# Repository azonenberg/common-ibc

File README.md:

# common-ibc

This is a 48-12V 72W non-isolated intermediate bus converter which I plan to use in all of my larger FPGA projects.

It uses a charge pump which has a fixed divide-by-4 output ratio rather than using a regulating buck topology. This
allows high efficiency but requires downstream loads to be able to tolerate a wider range of input voltages.

The architecture is scalable to 2 or 4 parallel converter modules, allowing 144W (12A) or 288W (24A) IBCs based on the
same chipset to be constructed in a straightforward manner based on a scaling of this design, however there are no
near-term plans to create such a converter since none of my near term project plans require that much power.

## Input

The input is +48VDC nominal on a 6-pin Molex Mini-Fit Jr connector, using a pinout compatible with the Mean Well
GST280A48-C6P power brick (and possibly others). The negative terminal of the input power connection is connected to
circuit ground.

The permissible operating range is 40 to 56VDC (corresponding to 10 to 14V output). An input protection circuit will
disable the converter if the input is out of this range.

The unregulated output voltage is 1/4 of the input, so if the load has tighter requirements for accuracy of the 12V
rail then this will further constrain the input supply voltage.

## Internal Construction

The converter is built around the Murata MYC0409-NA charge pump DC-DC module.

## Outputs

In addition to the high current 12V output (on an 8-pin Molex Mini-Fit Jr connector) the converter provides a 3.3V
standby rail (using the Cyntec MUN12AD03-SE regulating off of the 12V rail), capable of up to 3A, which is intended for
powering sleep/idle circuitry such as soft power on/off, rail sequencing, etc.

Both the primary 12V step-down converter and the 3.3V standby regulator are always enabled, however a load switch on
the main 12V output allows it to be disabled to completely power down the bulk of the downstream device, keeping only
the converter board and the 3V3_SB rail on the downstream device energized. The load switch has an integrated soft
start, preventing high current surges when charging bulk capacitance on the load.

## Monitoring

The onboard STM32L431 microcontroller monitors the PGOOD signals of internal regulators as well as the ALERT output
of the onboard AT30TS74 temperature sensor. It also continually uses an internal ADC to record the input and output
voltage, downstream load sense voltage, and input and output current. All of these sensor readings may be queried by
the load over the I2C management bus.

## Protection

The converter includes multiple levels of protection to minimize the risk of fire or equipment damage.

The most critical interlocks are implemented in hardware while additional protections with lower thresholds are
implemented in software on the management MCU.

If a software interlock triggers, the 12V output is disabled. The management MCU will automatically attempt to restart
the output (as long as the load is still requesting power) at periodic intervals once the fault condition is cleared.

The 3.3V standby output will remain active and the management MCU will remain operational while a software interlock is
tripped.

### Input overcurrent

The 48V input is fused at 2.5A using a socketed 5x20mm fast-blow fuse.

### Output overcurrent

The 12V primary output is fused at 10A using a soldered-down fast-blow fuse.

The 3.3V standby output is current limited (typical range 3.8 - 5.2A) by the DC-DC converter and does not have an
supplemental fuse.

If the 12V output current exceeds 6.5A, a software interlock is triggered. The output load switch also has a
short circuit protection feature, however the software interlock is intended to trip at a lower level.

### Regulator fault

If any of the internal regulators indicates a problem (PGOOD low) a software interlock is triggered.

### Over-temperature

If the AT30TS74 indicates an out-of-bounds temperature (ALERT low) a software interlock is triggered.

The MCU does not configure the AT30TS74; on power up the default over-temperature limit (80C) is active. This sensor is
located on the same I2C management bus as the MCU and may be reconfigured or queried by the load as required; the
IBC will activate the interlock if the programmed temperature range is exceeded.

### Input under / over voltage

The input is monitored by a TPS16630 protection controller, which also provides soft-start for the input bulk
capacitance. If the input voltage drops below 40V or rises above 56V (corresponding to 10-14V output) the system will
shut down completely (input power cut off upstream of the charge pump, disabling the microcontroller, 3.3V standby
rail, and all internal circuitry past the protection controller).

The input has a Schottky diode to ground in reverse polarity. If the input goes significantly negative (reverse
polarity connection) the diode will conduct and blow the input fuse, hopefully protecting the load and possibly even
the power supply from damage.

As an additional protection against catastrophic overvoltage at the input, a zener clamp will trip at approximately
58V, blowing the input fuse.

### Output under / over voltage

Since the output voltage is normally a fixed 4:1 scaling of the input, output voltage drifting beyond this range is
likely indicative of a failure of the charge pump module.

* If the 12V rail voltage drops below 10V, a software interlock is triggered.
* If the 12V rail voltage rises above 14V, a software interlock is triggered.
* If the 12V rail voltage rises above 17V a zener clamp on the output will begin to conduct, blowing the output fuse.

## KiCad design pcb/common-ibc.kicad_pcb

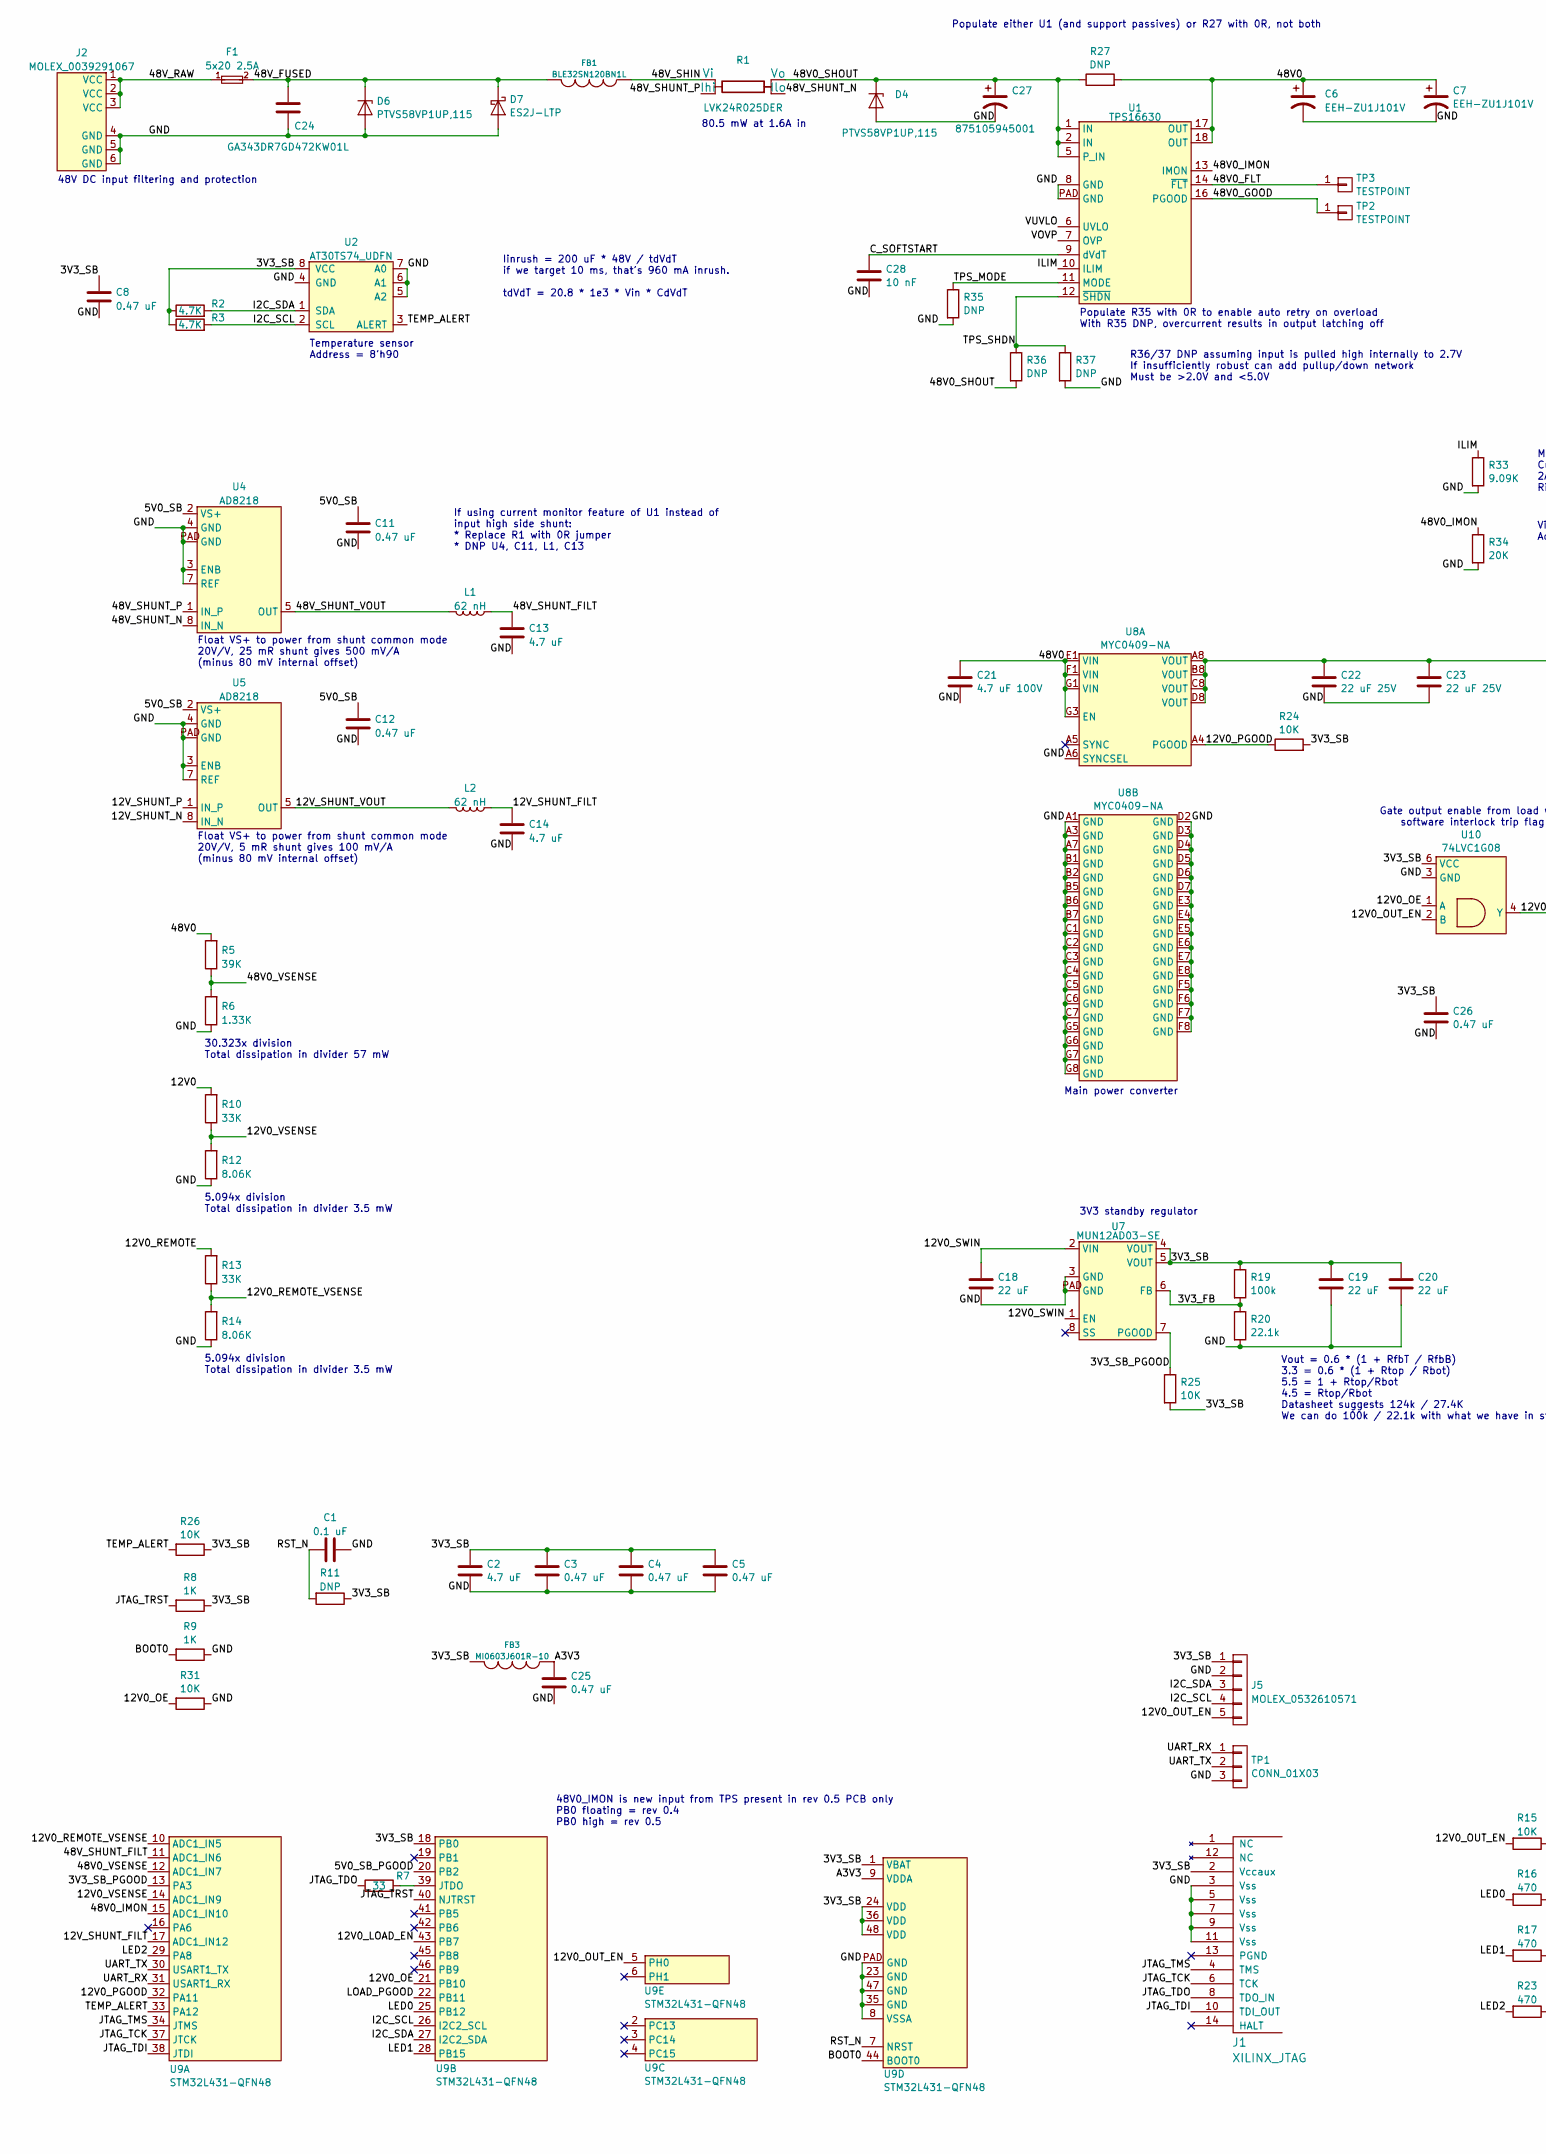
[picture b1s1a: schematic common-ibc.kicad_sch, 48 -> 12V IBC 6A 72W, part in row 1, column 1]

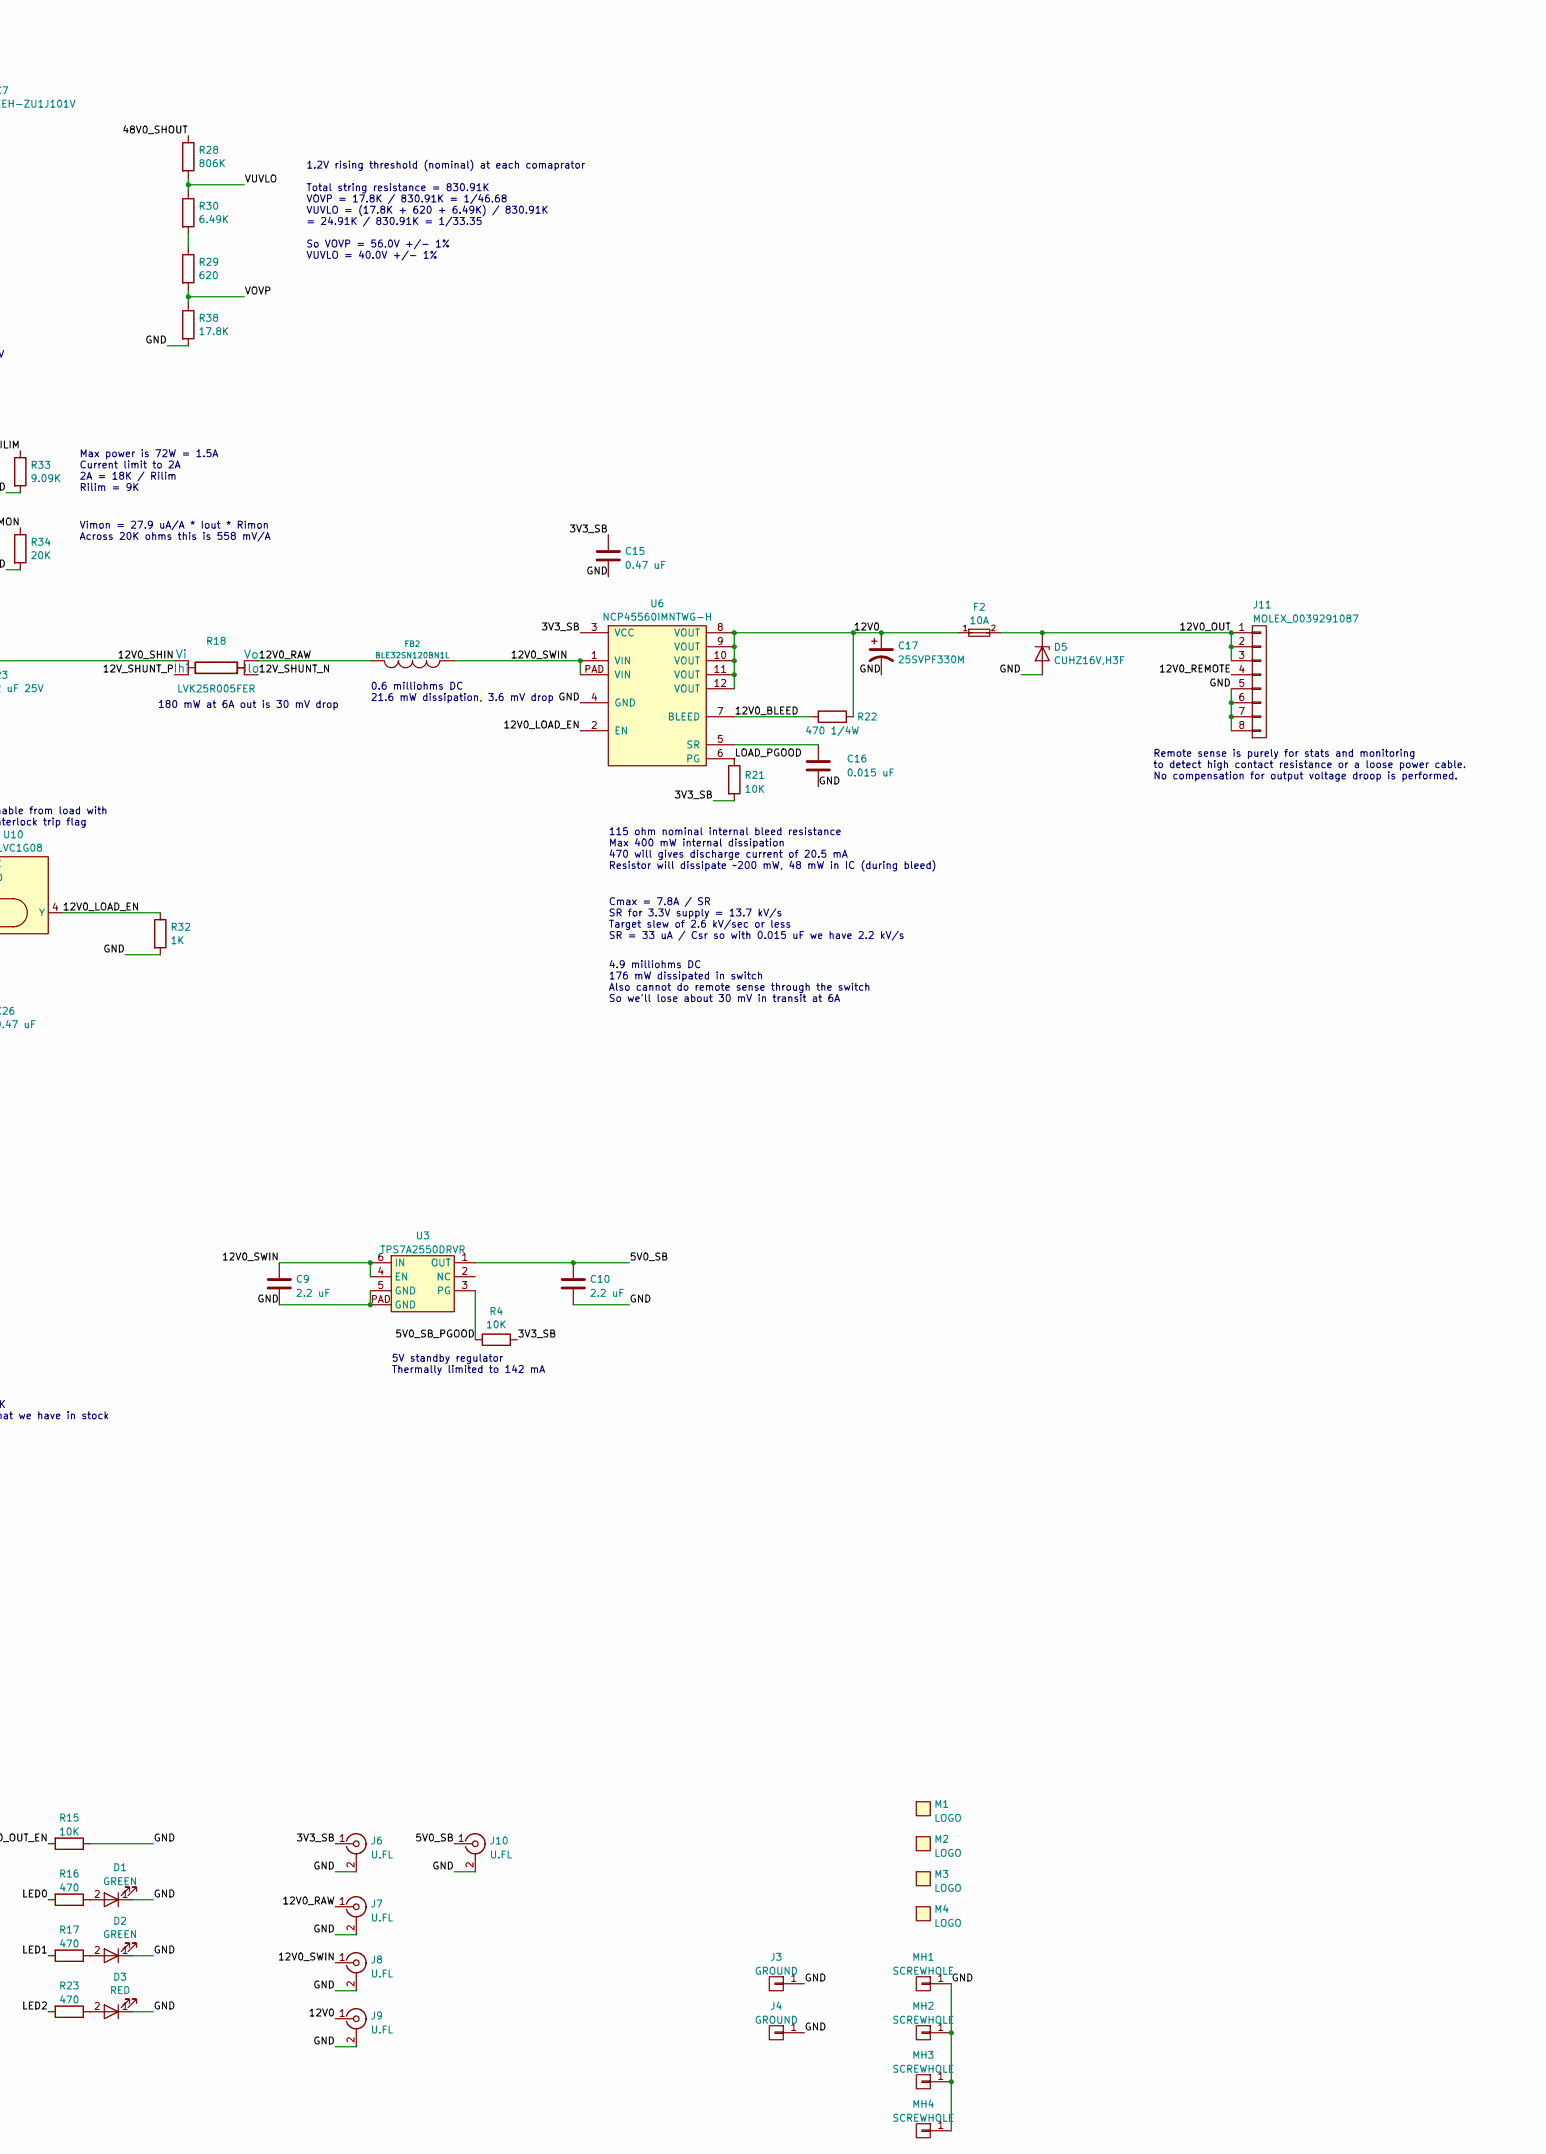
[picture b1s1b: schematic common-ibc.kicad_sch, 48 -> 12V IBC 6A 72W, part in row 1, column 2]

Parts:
C1: 0.1 uF; EIA_0402_CAP_NOSILK
C2, C13, C14: 4.7 uF; EIA_0603_CAP_NOSILK
C3, C4, C5, C8, C11, C12, C15, C25, C26: 0.47 uF; EIA_0402_CAP_NOSILK
C6, C7: EEH-ZU1J101V; CAP_AL_10MM_SMT
C9, C10: 2.2 uF; EIA_0805_CAP_NOSILK
C16: 0.015 uF; EIA_0603_CAP_NOSILK
C17: 25SVPF330M; CAP_AL_10MM_SMT
C18: 22 uF; EIA_1812_CAP_NOSILK
C19, C20: 22 uF; EIA_1210_CAP_NOSILK
C21: 4.7 uF 100V; CAP_TDK_CKG57K
C22, C23: 22 uF 25V; EIA_1812_CAP_NOSILK
C24: GA343DR7GD472KW01L; EIA_1812_CAP_NOSILK
C27: 875105945001; CAP_AL_6.3MM_SMT
C28: 10 nF; EIA_0402_CAP_NOSILK
D1, D2: GREEN; EIA_0603_LED
D3: RED; EIA_0603_LED
D4, D6: PTVS58VP1UP,115; SOD128
D5: CUHZ16V,H3F; SOD323H
D7: ES2J-LTP; SMA
F1: 5x20 2.5A; FUSEHOLDER_KEYSTONE_4527
F2: 10A; EIA_1206_FUSE_NOSILK
FB1, FB2: BLE32SN120BN1L; EIA_1210_CAP_NOSILK
FB3: MI0603J601R-10; EIA_0603_INDUCTOR_NOSILK
J1: XILINX_JTAG; XILINX_JTAG_PTH_MOLEX_0878311420
J2: MOLEX_0039291067; CONN_MOLEX_MINIFITJR_6POS_0039291067
J3, J4: GROUND; TESTPOINT_SMT_KEYSTONE_5016
J5: MOLEX_0532610571; CONN_MOLEX_PICOBLADE_5POS_0532610571
J6, J7, J8, J9, J10: U.FL; CONN_U.FL_TE_1909763-1
J11: MOLEX_0039291087; CONN_MOLEX_MINIFITJR_8POS_0039291087
L1, L2: 62 nH; EIA_0402_CAP_NOSILK
M1: LOGO; LONGTHING-1200DPI
M2: LOGO; Logo_silk_OSHW_6x6mm
M3: LOGO; Logo_silk_ROHS_5x2.8mm
M4: LOGO; Logo_silk_WEEE_3.4x5mm
MH1, MH2, MH3, MH4: SCREWHOLE; MECHANICAL_CLEARANCEHOLE_4_40
R1: LVK24R025DER; OHMITE_LVK24
R2, R3: 4.7K; EIA_0402_RES_NOSILK
R4, R15, R21, R24, R25, R26, R31: 10K; EIA_0402_RES_NOSILK
R5: 39K; EIA_0402_RES_NOSILK
R6: 1.33K; EIA_0402_RES_NOSILK
R7: 33; EIA_0402_RES_NOSILK
R8, R9, R32: 1K; EIA_0402_RES_NOSILK
R10, R13: 33K; EIA_0402_RES_NOSILK
R11, R35, R37: DNP; EIA_0402_RES_NOSILK
R12, R14: 8.06K; EIA_0402_RES_NOSILK
R16, R17, R23: 470; EIA_0402_RES_NOSILK
R18: LVK25R005FER; OHMITE_LVK25
R19: 100k; EIA_0402_RES_NOSILK
R20: 22.1k; EIA_0402_RES_NOSILK
R22: 470 1/4W; EIA_0603_RES_NOSILK
R27: DNP; EIA_0805_CAP_NOSILK
R28: 806K; EIA_0603_RES_NOSILK
R29: 620; EIA_0402_RES_NOSILK
R30: 6.49K; EIA_0402_RES_NOSILK
R33: 9.09K; EIA_0402_RES_NOSILK
R34: 20K; EIA_0402_RES_NOSILK
R36: DNP; EIA_0603_RES_NOSILK
R38: 17.8K; EIA_0402_RES_NOSILK
TP1: CONN_01X03; CONN_HEADER_2.54MM_1x3
TP2, TP3: TESTPOINT; TESTPOINT_SMT_0.5MM
U1: TPS16630; QFN_24_0.5MM_4x4MM
U2: AT30TS74_UDFN; DFN_8_0.5MM_2x3MM_TALL
U3: TPS7A2550DRVR; DFN_6_0.65MM_2x2MM
U4, U5: AD8218; DFN_8_0.5MM_2x3MM_TALL
U6: NCP45560IMNTWG-H; DFN_12_0.5MM_3x3MM
U7: MUN12AD03-SE; MODULE_CYNTEC_MUN12AD03-SE
U8: MYC0409-NA; MODULE_MURATA_MYC0409-NA
U9: STM32L431-QFN48; QFN_48_0.5MM_7x7MM
U10: 74LVC1G08; DFN_6_0.5MM_1.4x1.00MM_NXP_X2-DFN1410-6

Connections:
/3V3_FB: R19.2, R20.1, U7.6 (FB)
/3V3_SB: C2.1, C3.1, C4.1, C5.1, C8.1, C15.1, C19.1, C20.1, C26.1, FB3.2, J1.2 (Vccaux), J5.1, J6.1 (In), R2.1, R3.1, R4.2, R8.1, R11.1, R19.1, R21.2, R24.2, R25.2, R26.1, U2.8 (VCC), U6.3 (VCC), U7.4 (VOUT), U7.5 (VOUT), U9.1 (VBAT), U9.18 (PB0), U9.24 (VDD), U9.36 (VDD), U9.48 (VDD), U10.6 (VCC)
/3V3_SB_PGOOD: R25.1, U7.7 (PGOOD), U9.13 (PA3)
/5V0_SB: C10.1, C11.1, C12.1, J10.1 (In), U3.1 (OUT), U4.2 (VS+), U5.2 (VS+)
/5V0_SB_PGOOD: R4.1, U3.3 (PG), U9.20 (PB2)
/12V0: C17.1, F2.1, J9.1 (In), R10.2, R22.2, U6.8 (VOUT), U6.9 (VOUT), U6.10 (VOUT), U6.11 (VOUT), U6.12 (VOUT)
/12V0_BLEED: R22.1, U6.7 (BLEED)
/12V0_LOAD_EN: R32.1, U6.2 (EN), U9.43 (PB7), U10.4 (Y)
/12V0_OE: R31.2, U9.21 (PB10), U10.1 (A)
/12V0_OUT: D5.1 (K), F2.2, J11.1, J11.2, J11.3
/12V0_OUT_EN: J5.5, R15.2, U9.5 (PH0), U10.2 (B)
/12V0_PGOOD: R24.1, U8.A4 (PGOOD), U9.32 (PA11)
/12V0_RAW: FB2.2, J7.1 (In), R18.2 (Vo)
/12V0_REMOTE: J11.4, R13.2
/12V0_REMOTE_VSENSE: R13.1, R14.2, U9.10 (ADC1_IN5)
/12V0_SHIN: C22.1, C23.1, R18.4 (Vi), U8.A8 (VOUT), U8.B8 (VOUT), U8.C8 (VOUT), U8.D8 (VOUT)
/12V0_SWIN: C9.1, C18.1, FB2.1, J8.1 (In), U3.4 (EN), U3.6 (IN), U6.1 (VIN), U6.PAD (VIN), U7.1 (EN), U7.2 (VIN)
/12V0_VSENSE: R10.1, R12.2, U9.14 (ADC1_IN9)
/12V_SHUNT_FILT: C14.2, L2.1, U9.17 (ADC1_IN12)
/12V_SHUNT_N: R18.1 (Ilo), U5.8 (IN_N)
/12V_SHUNT_P: R18.3 (Ihi), U5.1 (IN_P)
/12V_SHUNT_VOUT: L2.2, U5.5 (OUT)
/48V0: C6.1, C7.1, C21.1, R5.2, R27.2, U1.17 (OUT), U1.18 (OUT), U8.E1 (VIN), U8.F1 (VIN), U8.G1 (VIN), U8.G3 (EN)
/48V0_FLT: TP3.1, U1.14 (~FLT)
/48V0_GOOD: TP2.1, U1.16 (PGOOD)
/48V0_IMON: R34.1, U1.13 (IMON), U9.15 (ADC1_IN10)
/48V0_SHOUT: C27.1, D4.1 (K), R1.2 (Vo), R27.1, R28.1, R36.2, U1.1 (IN), U1.2 (IN), U1.5 (P_IN)
/48V0_VSENSE: R5.1, R6.2, U9.12 (ADC1_IN7)
/48V_FUSED: C24.1, D6.1 (K), D7.1 (K), F1.2, FB1.2
/48V_RAW: F1.1, J2.1 (VCC), J2.2 (VCC), J2.3 (VCC)
/48V_SHIN: FB1.1, R1.4 (Vi)
/48V_SHUNT_FILT: C13.2, L1.1, U9.11 (ADC1_IN6)
/48V_SHUNT_N: R1.1 (Ilo), U4.8 (IN_N)
/48V_SHUNT_P: R1.3 (Ihi), U4.1 (IN_P)
/48V_SHUNT_VOUT: L1.2, U4.5 (OUT)
/A3V3: C25.1, FB3.1, U9.9 (VDDA)
/BOOT0: R9.2, U9.44 (BOOT0)
/C_SOFTSTART: C28.1, U1.9 (dVdT)
/GND: C1.2, C2.2, C3.2, C4.2, C5.2, C6.2, C7.2, C8.2, C9.2, C10.2, C11.2, C12.2, C13.1, C14.1, C15.2, C16.2, C17.2, C18.2, C19.2, C20.2, C21.2, C22.2, C23.2, C24.2, C25.2, C26.2, C27.2, C28.2, D1.1 (K), D2.1 (K), D3.1 (K), D4.2 (A), D5.2 (A), D6.2 (A), D7.2 (A), J1.3 (Vss), J1.5 (Vss), J1.7 (Vss), J1.9 (Vss), J1.11 (Vss), J2.4 (GND), J2.5 (GND), J2.6 (GND), J3.1, J4.1, J5.2, J6.2 (Ext), J7.2 (Ext), J8.2 (Ext), J9.2 (Ext), J10.2 (Ext), J11.5, J11.6, J11.7, J11.8, MH1.1, MH2.1, MH3.1, MH4.1, R6.1, R9.1, R12.1, R14.1, R15.1, R20.2, R31.1, R32.2, R33.2, R34.2, R35.2, R37.2, R38.2, TP1.3, U1.8 (GND), U1.PAD (GND), U2.4 (GND), U2.5 (A2), U2.6 (A1), U2.7 (A0), U3.5 (GND), U3.PAD (GND), U4.3 (ENB), U4.4 (GND), U4.7 (REF), U4.PAD (GND), U5.3 (ENB), U5.4 (GND), U5.7 (REF), U5.PAD (GND), U6.4 (GND), U7.3 (GND), U7.PAD (GND), U8.A1 (GND), U8.A3 (GND), U8.A6 (SYNCSEL), U8.A7 (GND), U8.B1 (GND), U8.B2 (GND), U8.B5 (GND), U8.B6 (GND), U8.B7 (GND), U8.C1 (GND), U8.C2 (GND), U8.C3 (GND), U8.C4 (GND), U8.C5 (GND), U8.C6 (GND), U8.C7 (GND), U8.D2 (GND), U8.D3 (GND), U8.D4 (GND), U8.D5 (GND), U8.D6 (GND), U8.D7 (GND), U8.E3 (GND), U8.E4 (GND), U8.E5 (GND), U8.E6 (GND), U8.E7 (GND), U8.E8 (GND), U8.F5 (GND), U8.F6 (GND), U8.F7 (GND), U8.F8 (GND), U8.G5 (GND), U8.G6 (GND), U8.G7 (GND), U8.G8 (GND), U9.8 (VSSA), U9.23 (GND), U9.35 (GND), U9.47 (GND), U9.PAD (GND), U10.3 (GND)
/I2C_SCL: J5.4, R3.2, U2.2 (SCL), U9.26 (I2C2_SCL)
/I2C_SDA: J5.3, R2.2, U2.1 (SDA), U9.27 (I2C2_SDA)
/ILIM: R33.1, U1.10 (ILIM)
/JTAG_TCK: J1.6 (TCK), U9.37 (JTCK)
/JTAG_TDI: J1.10 (TDI_OUT), U9.38 (JTDI)
/JTAG_TDO: J1.8 (TDO_IN), R7.1
/JTAG_TMS: J1.4 (TMS), U9.34 (JTMS)
/JTAG_TRST: R8.2, U9.40 (NJTRST)
/LED0: R16.2, U9.25 (PB12)
/LED1: R17.2, U9.28 (PB15)
/LED2: R23.2, U9.29 (PA8)
/LOAD_PGOOD: R21.1, U6.6 (PG), U9.22 (PB11)
/RST_N: C1.1, R11.2, U9.7 (NRST)
/TEMP_ALERT: R26.2, U2.3 (ALERT), U9.33 (PA12)
/TPS_MODE: R35.1, U1.11 (MODE)
/TPS_SHDN: R36.1, R37.1, U1.12 (~SHDN)
/UART_RX: TP1.1, U9.31 (USART1_RX)
/UART_TX: TP1.2, U9.30 (USART1_TX)
/VOVP: R29.2, R38.1, U1.7 (OVP)
/VUVLO: R28.2, R30.1, U1.6 (UVLO)
unnamed: D1.2 (A), R16.1
unnamed: D2.2 (A), R17.1
unnamed: D3.2 (A), R23.1
unnamed: R29.1, R30.2
unnamed: C16.1, U6.5 (SR)
unnamed: R7.2, U9.39 (JTDO)

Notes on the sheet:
80.5 mW at 1.6A in
Populate R35 with 0R to enable auto retry on overload With R35 DNP, overcurrent results in output latching off
115 ohm nominal internal bleed resistance Max 400 mW internal dissipation 470 will gives discharge current of 20.5 mA Resistor will dissipate ~200 mW, 48 mW in IC (during bleed)
1.2V rising threshold (nominal) at each comaprator Total string resistance = 830.91K VOVP = 17.8K / 830.91K = 1/46.68 VUVLO = (17.8K + 620 + 6.49K) / 830.91K = 24.91K / 830.91K = 1/33.35 So VOVP = 56.0V +/- 1% VUVLO = 40.0V +/- 1%
Iinrush = 200 uF * 48V / tdVdT if we target 10 ms, that's 960 mA inrush. tdVdT = 20.8 * 1e3 * Vin * CdVdT
Max power is 72W = 1.5A Current limit to 2A 2A = 18K / Rilim Rilim = 9K
Populate either U1 (and support passives) or R27 with 0R, not both
5V standby regulator Thermally limited to 142 mA
Vout = 0.6 * (1 + RfbT / RfbB) 3.3 = 0.6 * (1 + Rtop / Rbot) 5.5 = 1 + Rtop/Rbot 4.5 = Rtop/Rbot Datasheet suggests 124k / 27.4K We can do 100k / 22.1k with what we have in stock
48V0_IMON is new input from TPS present in rev 0.5 PCB only PB0 floating = rev 0.4 PB0 high = rev 0.5
180 mW at 6A out is 30 mV drop
30.323x division Total dissipation in divider 57 mW
Vimon = 27.9 uA/A * Iout * Rimon Across 20K ohms this is 558 mV/A
Temperature sensor Address = 8'h90
Float VS+ to power from shunt common mode 20V/V, 5 mR shunt gives 100 mV/A (minus 80 mV internal offset)
If using current monitor feature of U1 instead of input high side shunt: * Replace R1 with 0R jumper * DNP U4, C11, L1, C13
Float VS+ to power from shunt common mode 20V/V, 25 mR shunt gives 500 mV/A (minus 80 mV internal offset)
R36/37 DNP assuming input is pulled high internally to 2.7V If insufficiently robust can add pullup/down network Must be >2.0V and <5.0V
0.6 milliohms DC 21.6 mW dissipation, 3.6 mV drop
Cmax = 7.8A / SR SR for 3.3V supply = 13.7 kV/s Target slew of 2.6 kV/sec or less SR = 33 uA / Csr so with 0.015 uF we have 2.2 kV/s
Remote sense is purely for stats and monitoring to detect high contact resistance or a loose power cable. No compensation for output voltage droop is performed.
3V3 standby regulator
Gate output enable from load with software interlock trip flag
5.094x division Total dissipation in divider 3.5 mW
Main power converter
4.9 milliohms DC 176 mW dissipated in switch Also cannot do remote sense through the switch So we'll lose about 30 mV in transit at 6A
48V DC input filtering and protection

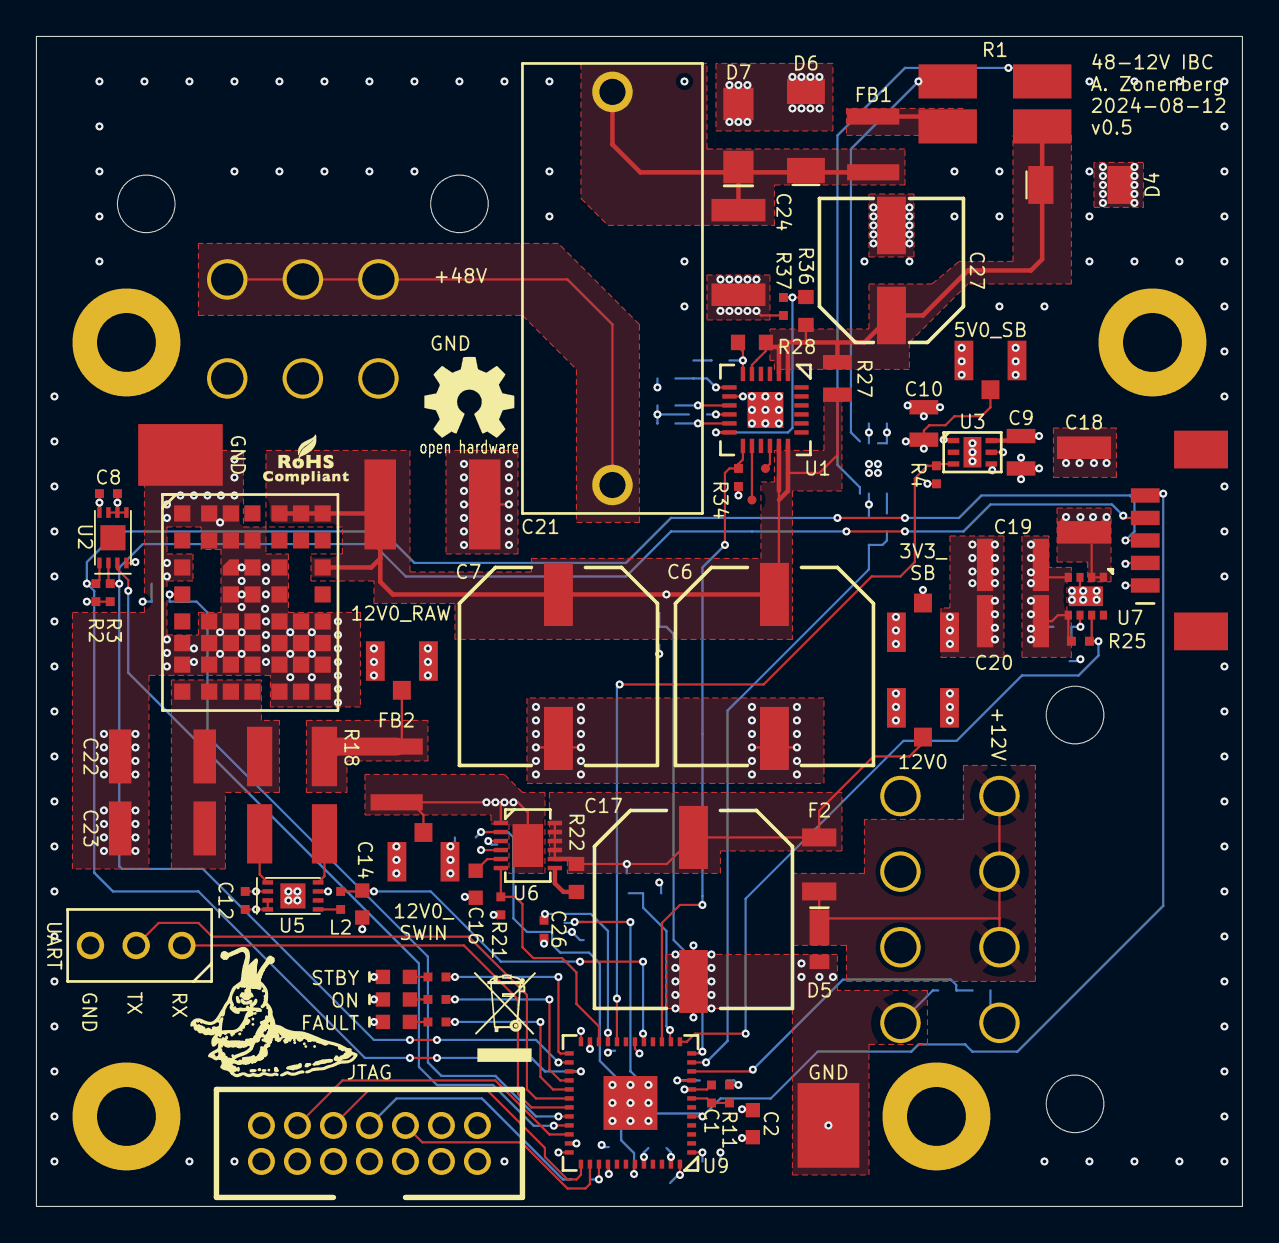
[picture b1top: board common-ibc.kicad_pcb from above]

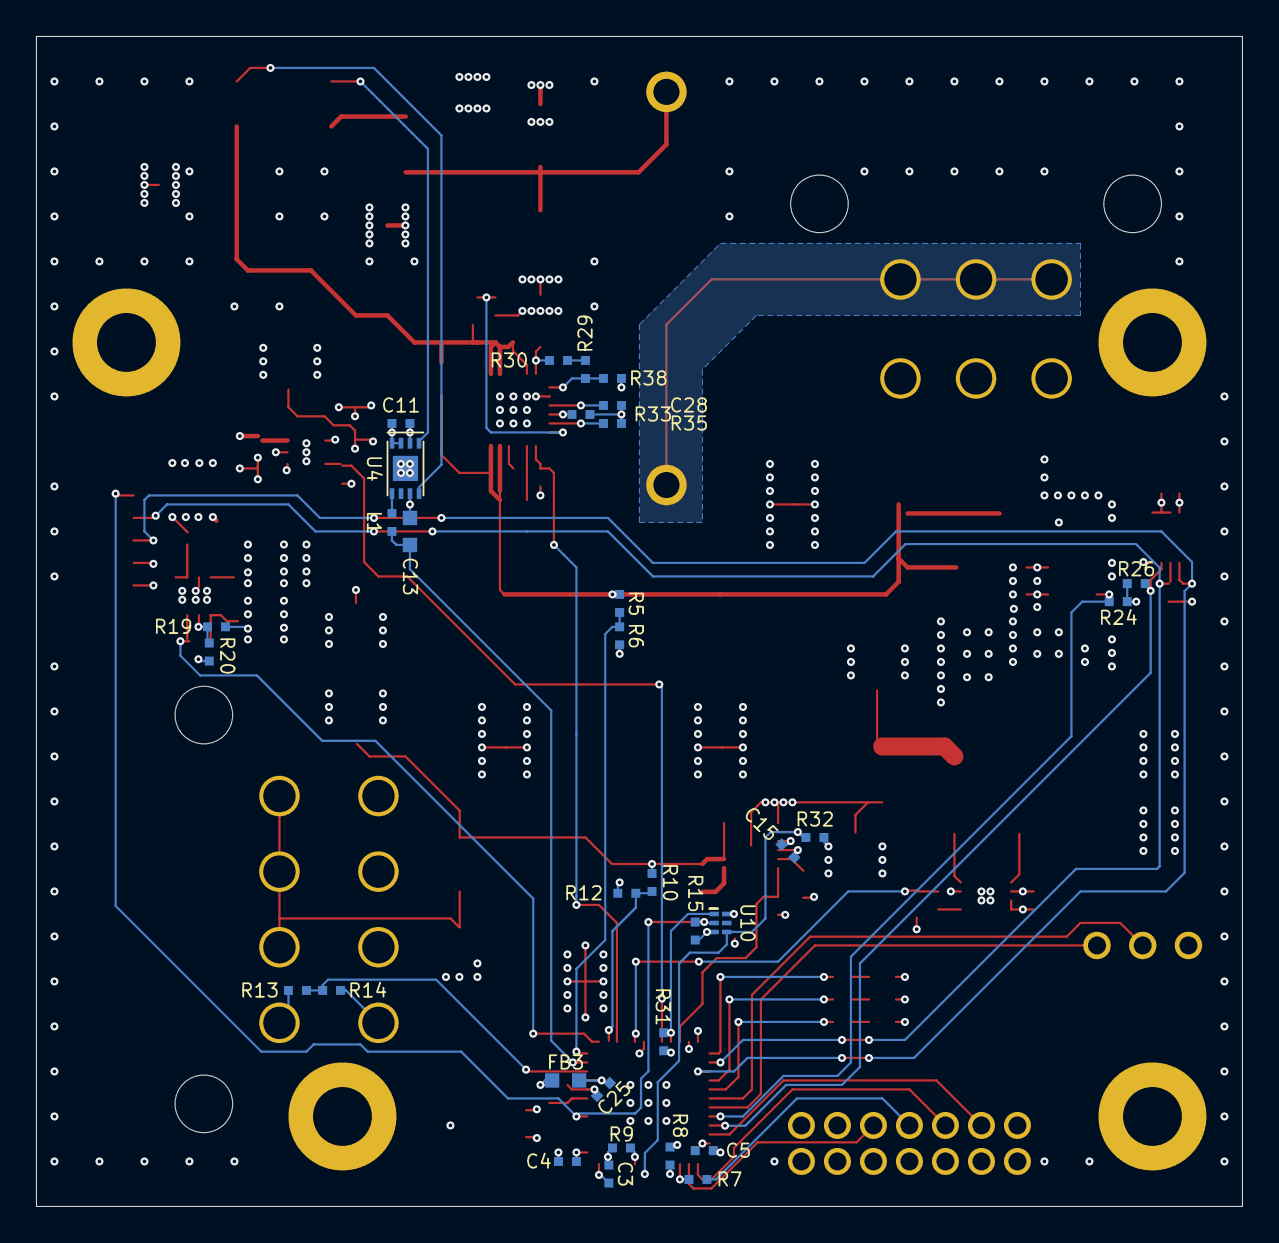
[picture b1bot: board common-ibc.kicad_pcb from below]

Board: 4 copper layers, 67.0 x 65.0 mm, 112 parts (33 on the bottom side), 65 nets.

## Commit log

2024-07-04 Initial IBC schematic passes ERC
2024-07-05 Most of the way done with layout
2024-07-06 Finished initial layout of IBC, ready for final review
2024-07-06 Minor silkscreen tweaks
2024-07-06 Finished layout review on IBC, made some tweaks to routing and solder paste
2024-07-06 Enlarged fuse holder annular ring
2024-07-08 Final version sent to fab for quotes
2024-07-08 Added gerber viewer project
2024-08-04 Added submodules for firmware support libraries
2024-08-04 Initial IBC bootloader
2024-08-04 Initial skeleton firmware for app partition
2024-08-04 Initial hard coded load enable for preliminary testing
2024-08-05 Now at minimum functional state with no I2C management support
2024-08-09 Initial I2C server class implementation
2024-08-09 Continued initial I2C server implementation
2024-08-09 Updated submodules
2024-08-10 Hopefully-mostly-done v0.5 layout
2024-08-10 Updated readme to describe new protection circuitry
2024-08-10 Request UL mark on front of PCB now
2024-08-10 IBC now reports input and output current via I2C properly
2024-08-11 Added I2C registers for MCU version, hardware version, MCU temperature, and 3V3_SB rail voltage
2024-08-11 Initial dummy CLI
2024-08-11 Added offset calibration coefficients stored in flash for both of the current shunt amplifiers
2024-08-12 Final v0.5 IBC design going to fab for quotes
2024-08-17 Converted over to CMake build flow, removed legacy makefiles
2024-08-23 Updated for latest libraries and enabled trace in debug builds
2024-09-08 Fixed typo in error message
2024-09-08 Added "output forceon" and "output normal" commands for load testing without a host board
2024-11-01 Initial refactoring to task model
2024-11-01 Output enable task
